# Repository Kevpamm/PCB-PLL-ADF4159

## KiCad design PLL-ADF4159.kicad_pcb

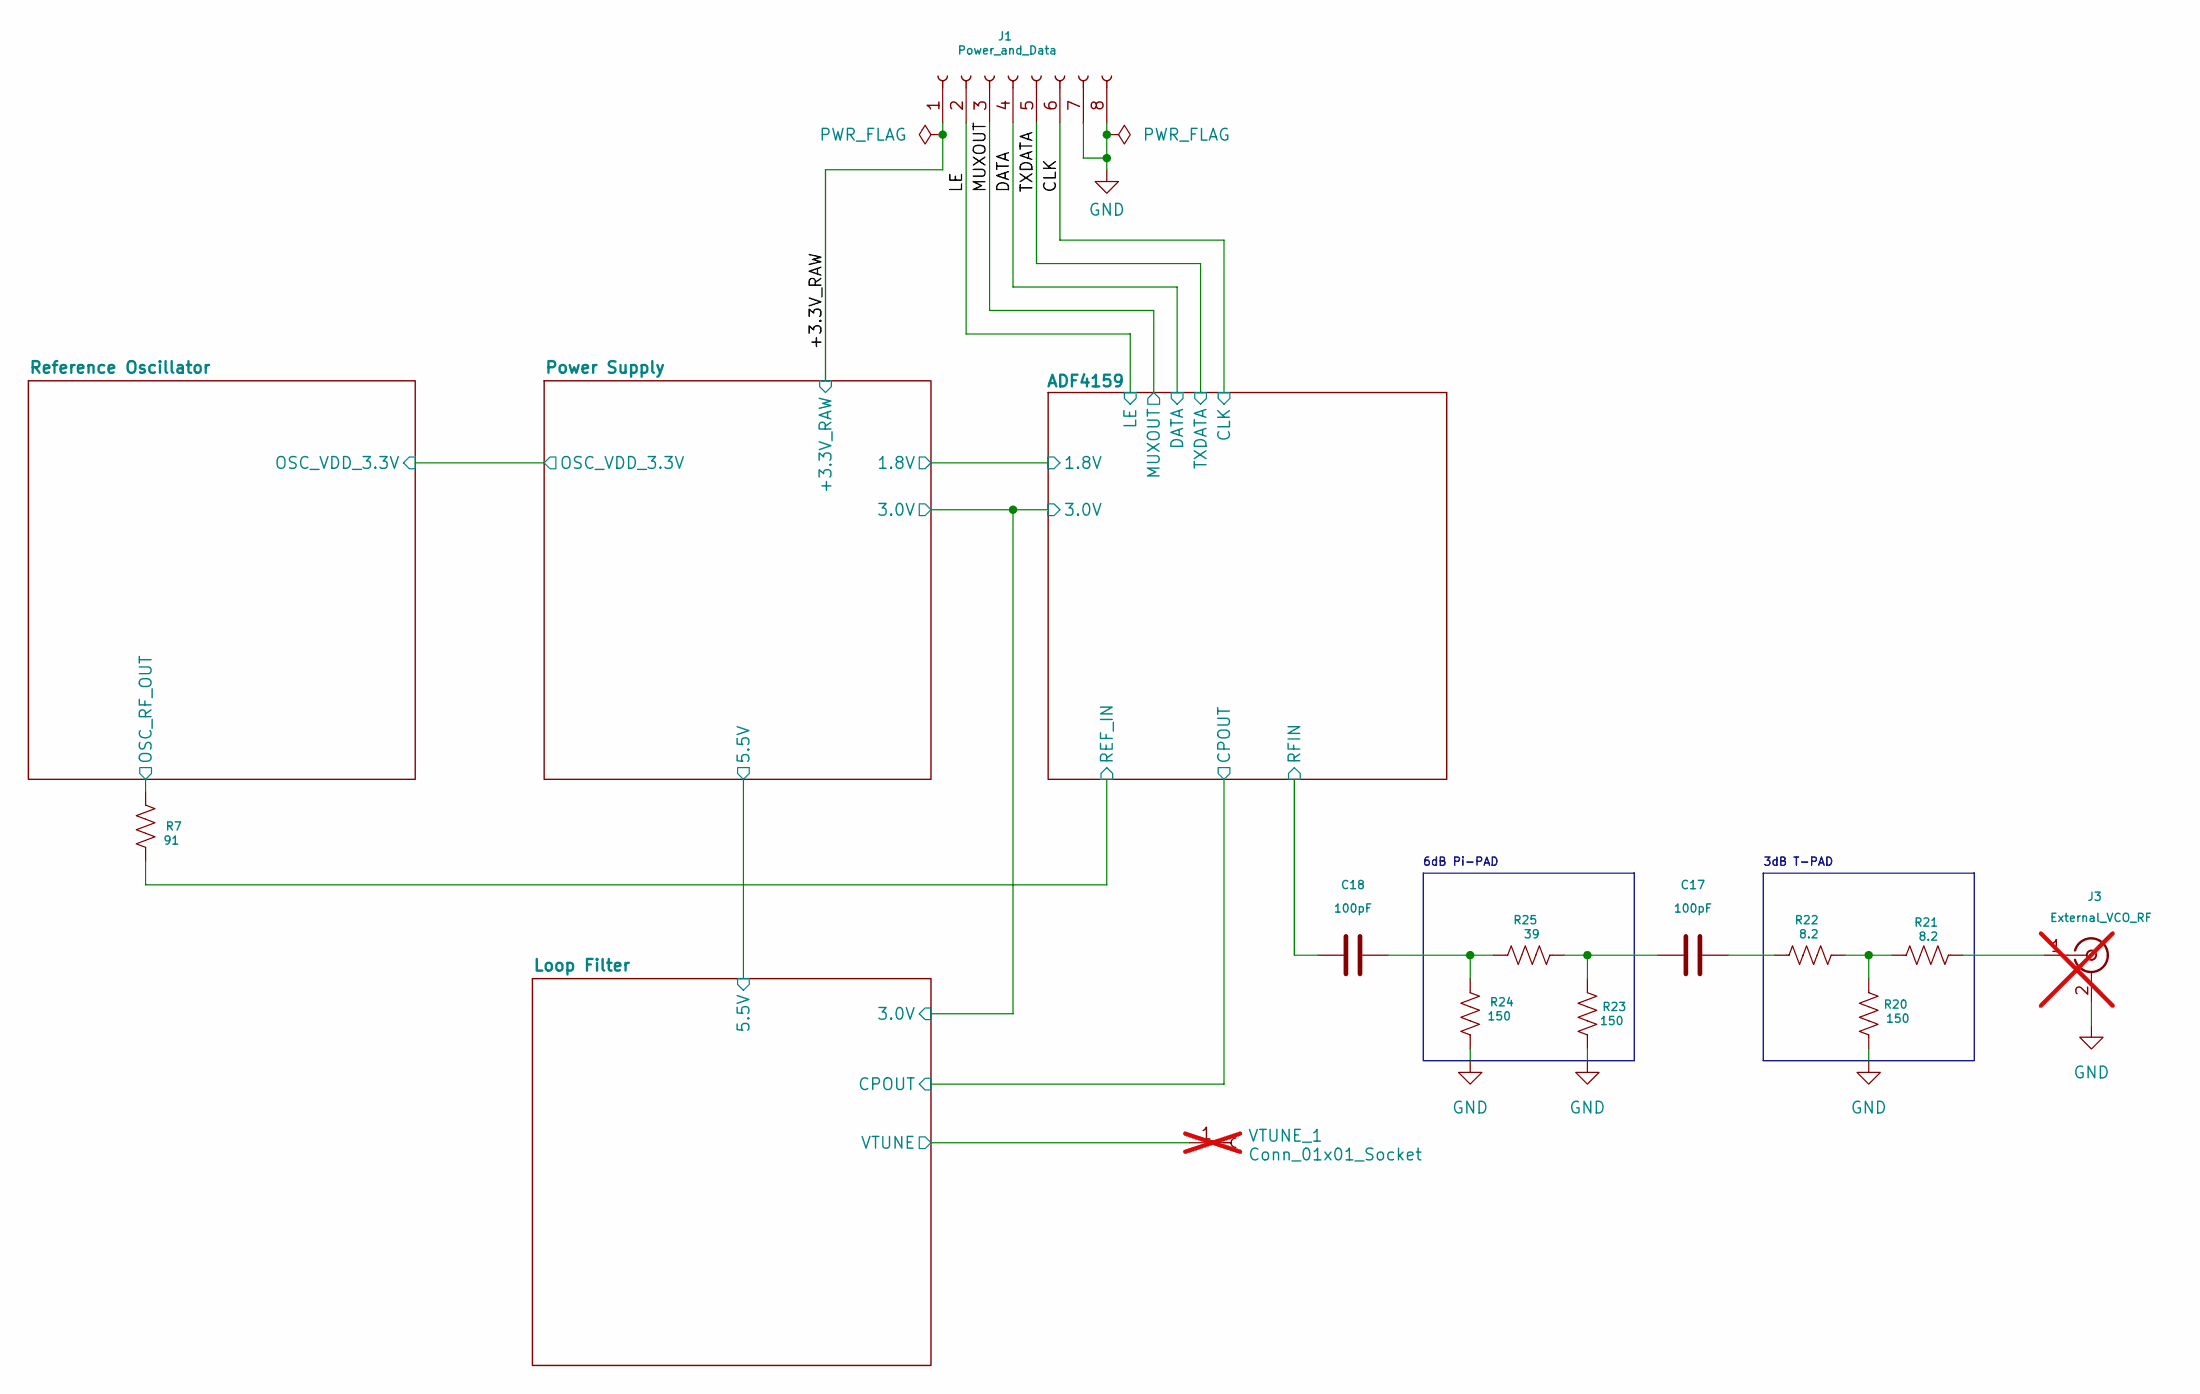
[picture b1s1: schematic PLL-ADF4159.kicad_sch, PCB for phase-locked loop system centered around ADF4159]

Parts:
C17, C18: 100pF; C_0402_1005Metric
J1: Power_and_Data; PinSocket_2x04_P2.54mm_Vertical
J3: External_VCO_RF; SMA_EDGELAUNCH_CUSTOME; not fitted
R7: 91; R_0402_1005Metric
R20: 150; R_0402_1005Metric
R21, R22: 8.2; R_0402_1005Metric; MFR.Part # RTT028R20FTH; JLCPCB Part # C4144
R23, R24: 150; R_0402_1005Metric; MFR.Part # CRCW0402150RFKED; JLCPCB Part # C82683
R25: 39; R_0402_1005Metric; MFR.Part # 0402WGF390JTCE; JLCPCB Part # C25110
VTUNE_1: Conn_01x01_Socket; PinSocket_1x01_P2.54mm_Vertical; not fitted

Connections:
/+3.3V_RAW: J1.1; also elsewhere on the board
/ADF4159/REF_IN: R7.2; also elsewhere on the board
/ADF4159/RFIN: C18.1; also elsewhere on the board
/CLK: J1.6; also elsewhere on the board
/DATA: J1.4; also elsewhere on the board
/LE: J1.2; also elsewhere on the board
/Loop Filter/VTUNE: VTUNE_1.1 (Pin_1_1); also elsewhere on the board
/MUXOUT: J1.3; also elsewhere on the board
/Reference Oscillator/OSC_RF_OUT: R7.1; also elsewhere on the board
/TXDATA: J1.5; also elsewhere on the board
GND: J1.7, J1.8, J3.2 (Ext), R20.2, R23.2, R24.2; also elsewhere on the board
unnamed: C17.1, R23.1, R25.2
unnamed: C17.2, R22.1
unnamed: C18.2, R24.1, R25.1
unnamed: J3.1 (In), R21.2
unnamed: R20.1, R21.1, R22.2

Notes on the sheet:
3dB T-PAD
6dB Pi-PAD

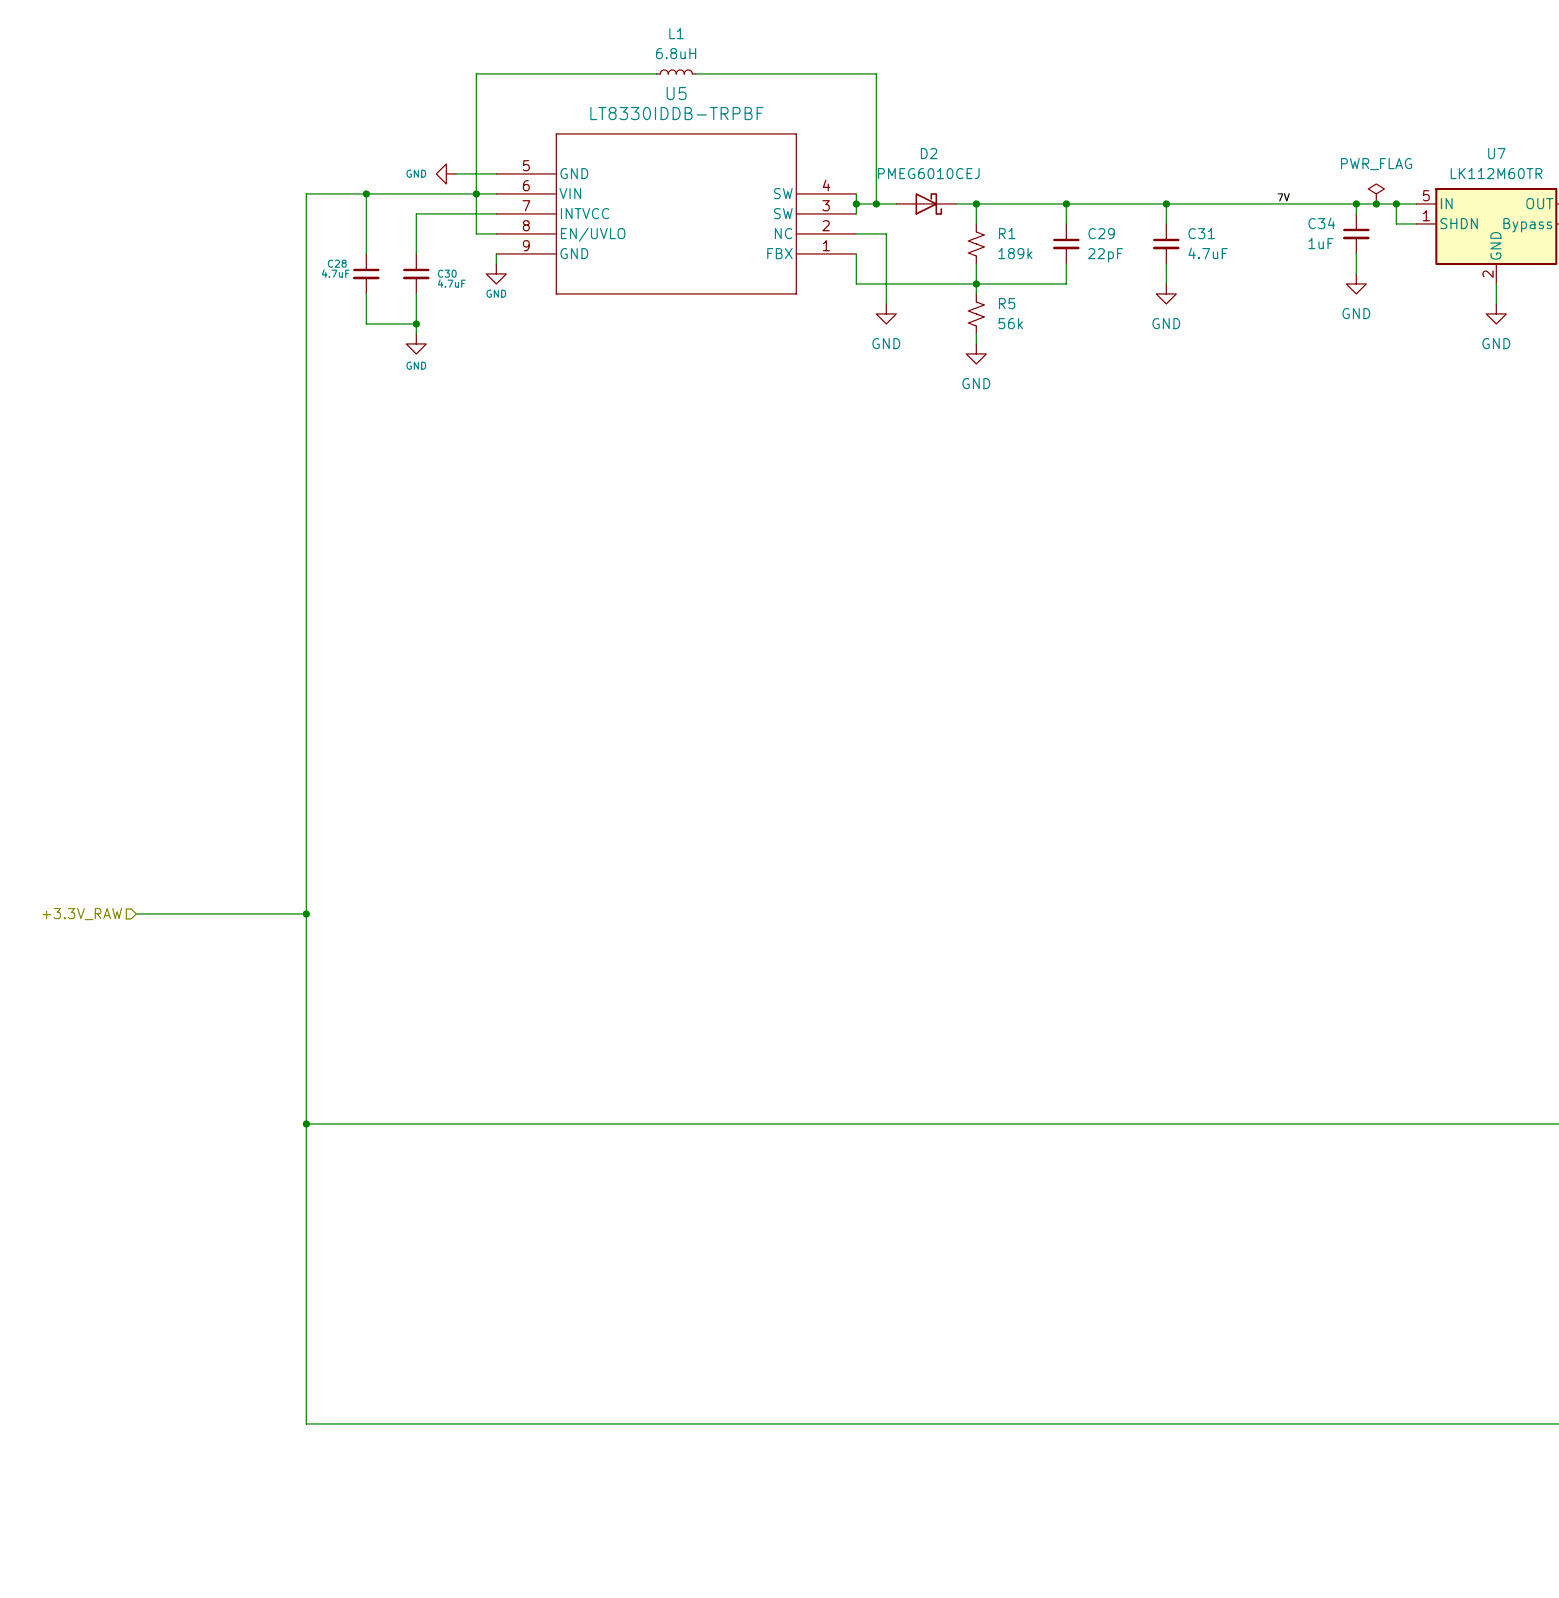
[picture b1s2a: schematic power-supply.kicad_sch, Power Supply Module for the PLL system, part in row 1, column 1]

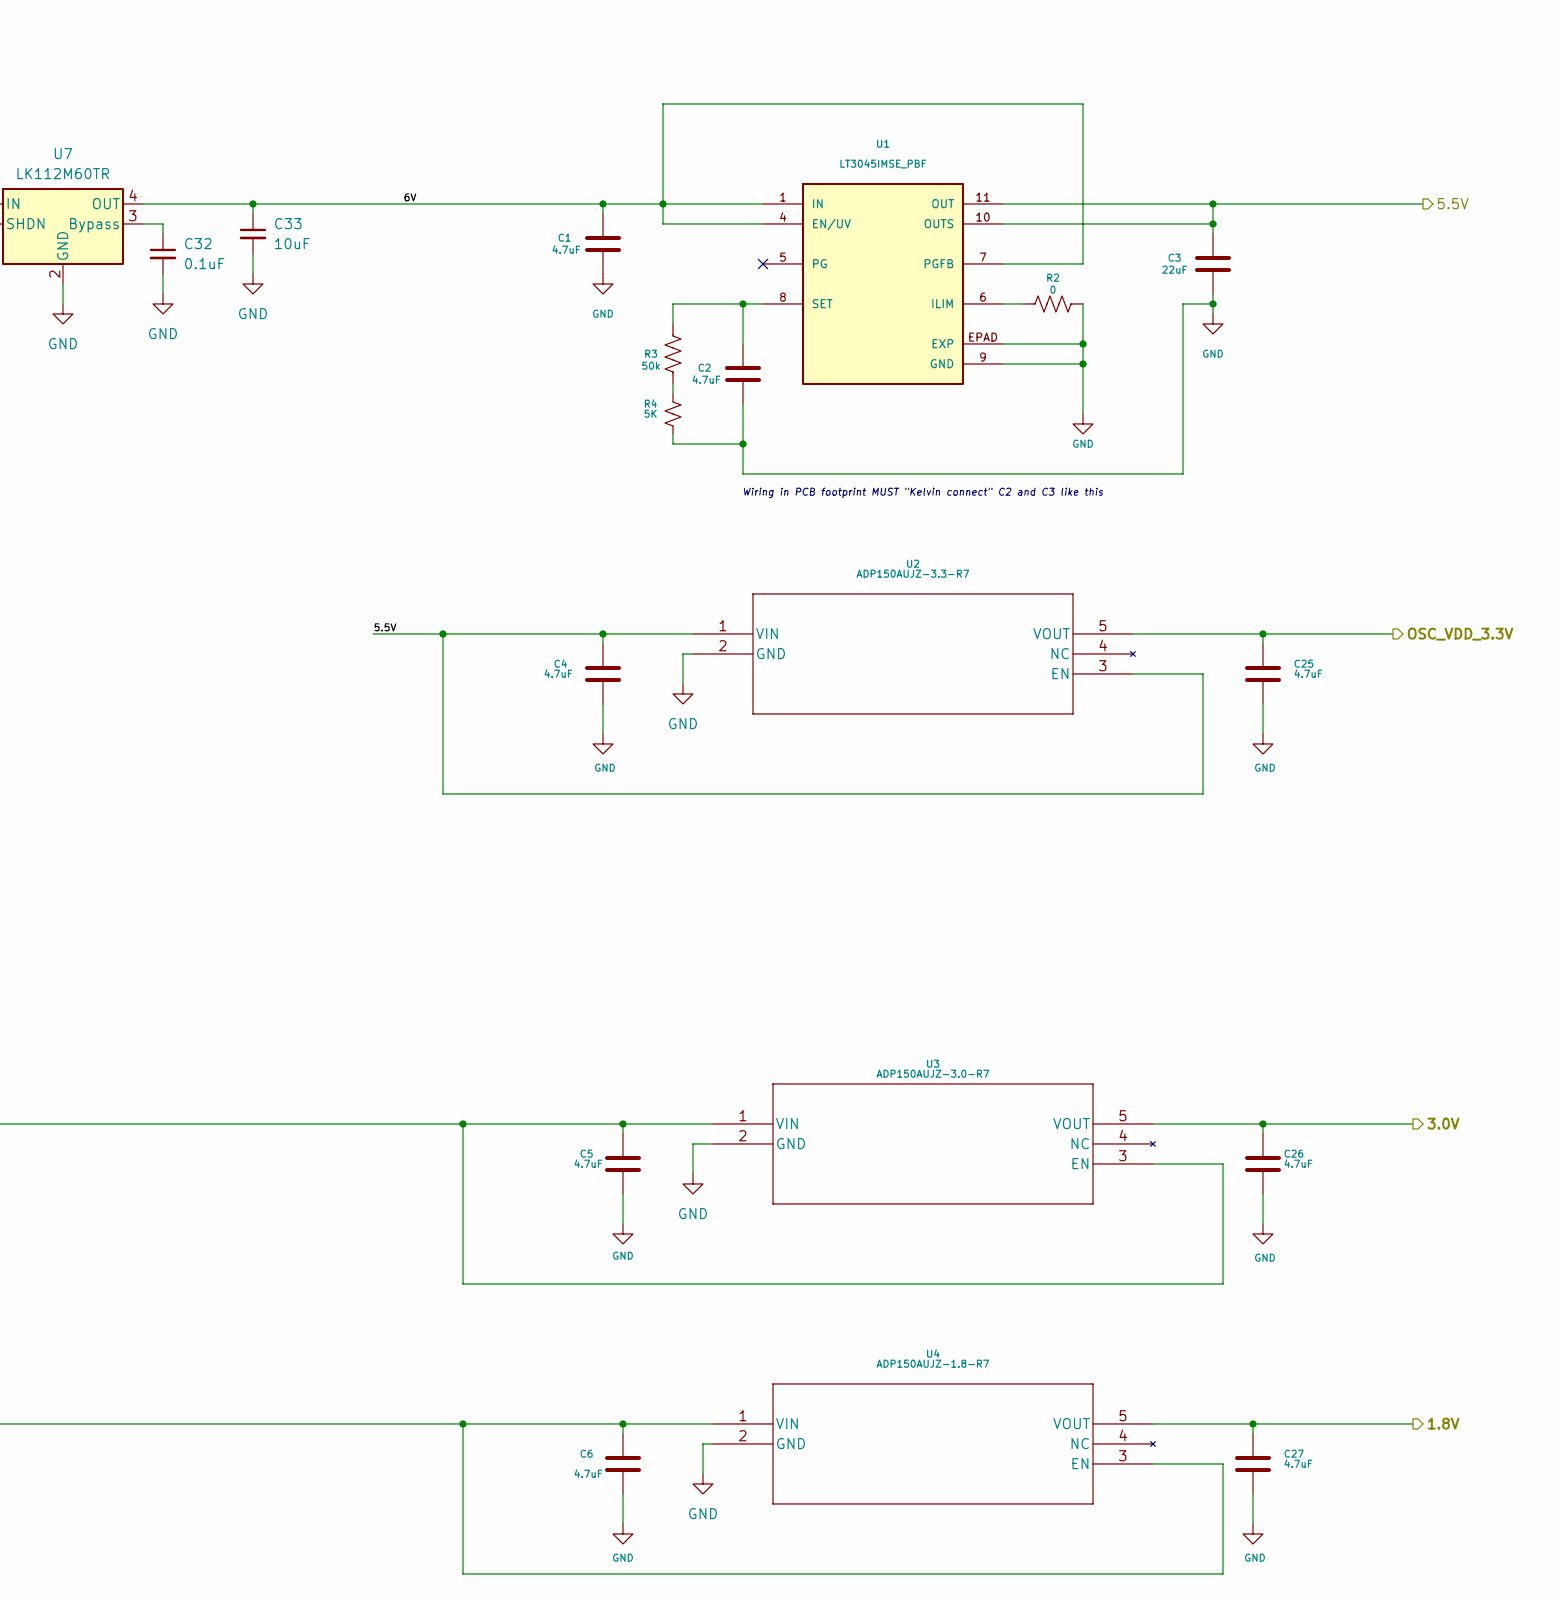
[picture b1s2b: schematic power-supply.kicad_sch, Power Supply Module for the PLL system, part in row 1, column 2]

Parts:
C1, C2, C4, C5, C6, C25, C26, C27, C28, C30, C31: 4.7uF; C_0402_1005Metric
C3: 22uF; C_0603_1608Metric
C29: 22pF; C_0402_1005Metric
C32: 0.1uF; C_0402_1005Metric
C33: 10uF; C_0603_1608Metric
C34: 1uF; C_0402_1005Metric
D2: PMEG6010CEJ; D_SOD-323F
L1: 6.8uH; L_0603_1608Metric
R1: 189k; R_0603_1608Metric
R2: 0; R_0402_1005Metric
R3: 50k; R_0402_1005Metric
R4: 5K; R_0402_1005Metric
R5: 56k; R_0805_2012Metric; MFR.Part # 0603WAF5602T5E; JLCPCB Part # C23206
U1: LT3045IMSE_PBF; MSOP12_MSE_ADI-L; PARTREV D
U2: ADP150AUJZ-3.3-R7; UJ_5_ADI-L
U3: ADP150AUJZ-3.0-R7; UJ_5_ADI-L
U4: ADP150AUJZ-1.8-R7; UJ_5_ADI-L
U5: LT8330IDDB-TRPBF; DDB_05-08-1702_ADI-L
U7: LK112M60TR; SOT-23-5

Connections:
/+3.3V_RAW: C5.1, C6.1, C28.1, L1.1, U3.1 (VIN), U3.3 (EN), U4.1 (VIN), U4.3 (EN), U5.6 (VIN), U5.8 (EN/UVLO); also elsewhere on the board
/ADF4159/1.8V: C27.1, U4.5 (VOUT); also elsewhere on the board
/ADF4159/3.0V: C26.1, U3.5 (VOUT); also elsewhere on the board
/Power Supply/5.5V: C3.1, C4.1, U1.10 (OUTS), U1.11 (OUT), U1.12 (OUT), U2.1 (VIN), U2.3 (EN); also elsewhere on the board
/Power Supply/6V: C1.1, C33.1, U1.1 (IN), U1.2 (IN), U1.3 (IN), U1.4 (EN/UV), U1.7 (PGFB), U7.4 (OUT)
/Power Supply/7V: C29.1, C31.1, C34.1, D2.1 (K), R1.2, U7.1 (SHDN), U7.5 (IN)
/Power Supply/OSC_VDD_3.3V: C25.1, U2.5 (VOUT); also elsewhere on the board
GND: C1.2, C2.2, C3.2, C4.2, C5.2, C6.2, C25.2, C26.2, C27.2, C28.2, C30.2, C31.2, C32.2, C33.2, C34.2, R2.1, R4.2, R5.1, U1.9 (GND), U1.EPAD (EXP), U2.2 (GND), U3.2 (GND), U4.2 (GND), U5.2 (NC), U5.5 (GND), U5.9 (GND), U7.2 (GND); also elsewhere on the board
unnamed: D2.2 (A), L1.2, U5.3 (SW), U5.4 (SW)
unnamed: R3.2, R4.1
unnamed: R2.2, U1.6 (ILIM)
unnamed: C2.1, R3.1, U1.8 (SET)
unnamed: C29.2, R1.1, R5.2, U5.1 (FBX)
unnamed: C30.1, U5.7 (INTVCC)
unnamed: C32.1, U7.3 (Bypass)

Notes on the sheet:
Wiring in PCB footprint MUST "Kelvin connect" C2 and C3 like this

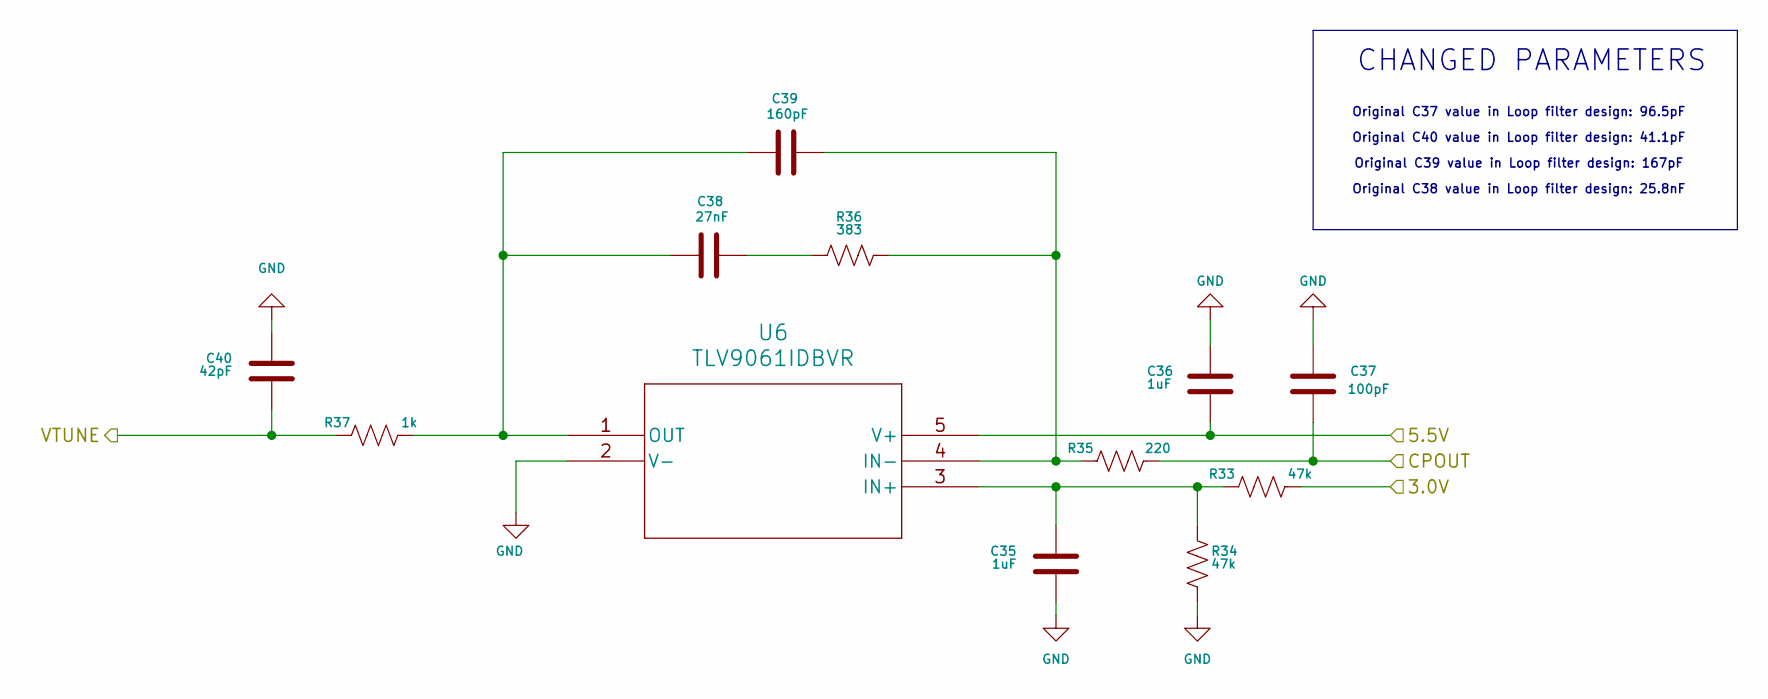
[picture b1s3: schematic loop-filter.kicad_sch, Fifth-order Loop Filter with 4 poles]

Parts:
C35, C36: 1uF; C_0402_1005Metric
C37: 100pF; C_0402_1005Metric
C38: 27nF; C_0402_1005Metric; MFR.Part # C1005X7R273KETS; JLCPCB Part # C147619
C39: 160pF; C_0402_1005Metric
C40: 42pF; C_0603_1608Metric; MFR.Part # 0603CG420J500NT; JLCPCB Part # C3008316
R33, R34: 47k; R_0402_1005Metric
R35: 220; R_0402_1005Metric
R36: 383; R_0402_1005Metric; MFR.Part # 0603WAF3830T5E; JLCPCB Part # C23036
R37: 1k; R_0402_1005Metric
U6: TLV9061IDBVR; DBV5_TEX

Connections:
/ADF4159/3.0V: R33.2; also elsewhere on the board
/ADF4159/CPOUT: C37.2, R35.2; also elsewhere on the board
/Loop Filter/VTUNE: C40.2, R37.2; also elsewhere on the board
/Power Supply/5.5V: C36.1, U6.5 (V+); also elsewhere on the board
GND: C35.2, C36.2, C37.1, C40.1, R34.2, U6.2 (V-); also elsewhere on the board
unnamed: C38.1, R36.1
unnamed: C35.1, R33.1, R34.1, U6.3 (IN+)
unnamed: C39.1, R35.1, R36.2, U6.4 (IN-)
unnamed: C38.2, C39.2, R37.1, U6.1 (OUT)

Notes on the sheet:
Original C40 value in Loop filter design: 41.1pF
Original C39 value in Loop filter design: 167pF
Original C38 value in Loop filter design: 25.8nF
Original C37 value in Loop filter design: 96.5pF
CHANGED PARAMETERS

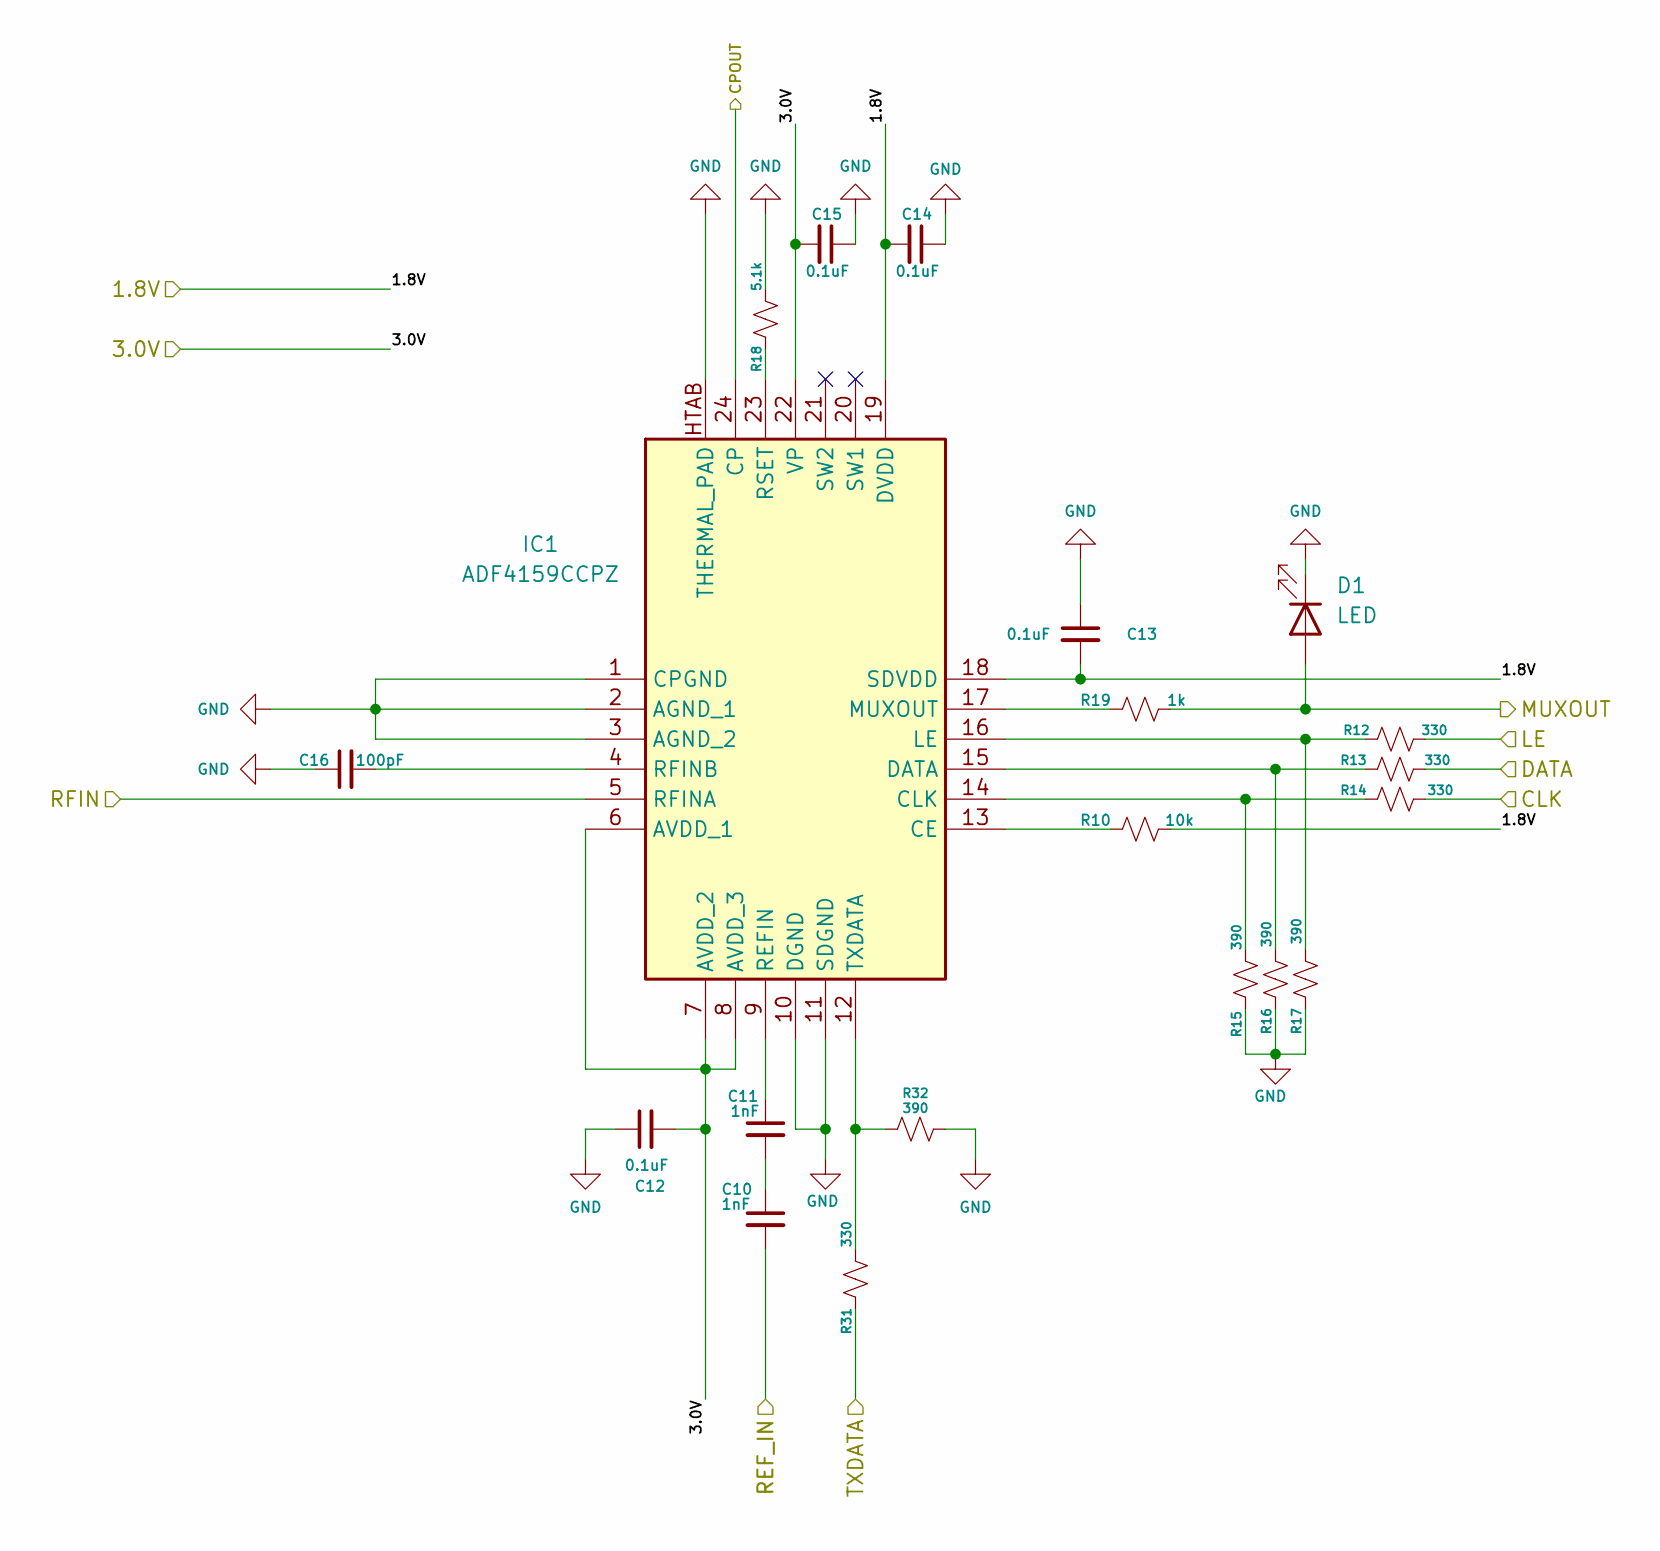
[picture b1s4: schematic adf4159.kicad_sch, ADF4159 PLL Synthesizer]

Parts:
C10, C11: 1nF; C_0402_1005Metric
C12, C13, C14, C15: 0.1uF; C_0402_1005Metric
C16: 100pF; C_0402_1005Metric
D1: LED; LED_0805_2012Metric
IC1: ADF4159CCPZ; CP_24_10_ADI-L; Manufacturer_Part_Number ADF4159CCPZ; Mouser Part Number 584-ADF4159CCPZ
R10: 10k; R_0402_1005Metric
R12, R13, R14, R31: 330; R_0402_1005Metric
R15, R16, R17, R32: 390; R_0402_1005Metric
R18: 5.1k; R_0402_1005Metric
R19: 1k; R_0402_1005Metric

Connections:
/ADF4159/1.8V: C13.2, C14.2, IC1.18 (SDVDD), IC1.19 (DVDD), R10.2; also elsewhere on the board
/ADF4159/3.0V: C12.2, C15.2, IC1.6 (AVDD_1), IC1.7 (AVDD_2), IC1.8 (AVDD_3), IC1.22 (VP); also elsewhere on the board
/ADF4159/CPOUT: IC1.24 (CP); also elsewhere on the board
/ADF4159/REF_IN: C10.2; also elsewhere on the board
/ADF4159/RFIN: IC1.5 (RFINA); also elsewhere on the board
/CLK: R14.2; also elsewhere on the board
/DATA: R13.2; also elsewhere on the board
/LE: R12.2; also elsewhere on the board
/MUXOUT: D1.2 (A), R19.2; also elsewhere on the board
/TXDATA: R31.1; also elsewhere on the board
GND: C12.1, C13.1, C14.1, C15.1, C16.1, D1.1 (K), IC1.1 (CPGND), IC1.2 (AGND_1), IC1.3 (AGND_2), IC1.10 (DGND), IC1.11 (SDGND), IC1.HTAB (THERMAL_PAD), R15.1, R16.1, R17.1, R18.1, R32.2; also elsewhere on the board
unnamed: C10.1, C11.2
unnamed: IC1.13 (CE), R10.1
unnamed: IC1.14 (CLK), R14.1, R15.2
unnamed: IC1.15 (DATA), R13.1, R16.2
unnamed: IC1.16 (LE), R12.1, R17.2
unnamed: IC1.17 (MUXOUT), R19.1
unnamed: C11.1, IC1.9 (REFIN)
unnamed: C16.2, IC1.4 (RFINB)
unnamed: IC1.23 (RSET), R18.2
unnamed: IC1.12 (TXDATA), R31.2, R32.1

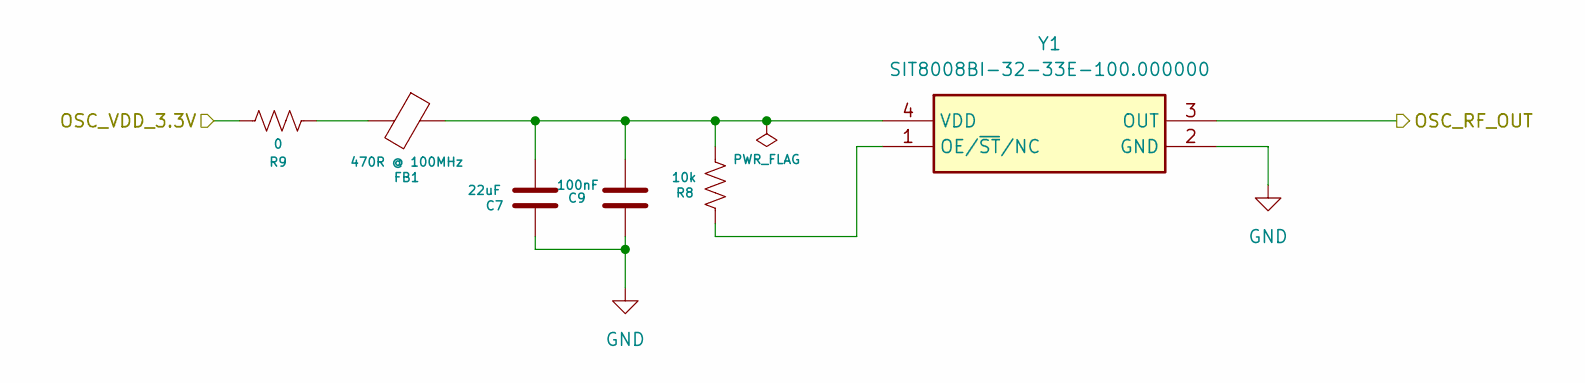
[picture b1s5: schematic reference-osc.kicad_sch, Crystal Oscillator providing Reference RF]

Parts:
C7: 22uF; C_0402_1005Metric
C9: 100nF; C_0402_1005Metric
FB1: 470R @ 100MHz; L_0603_1608Metric; MPN BLM18AG471SZ1D; JLCPCB part: C883591
R8: 10k; R_0402_1005Metric
R9: 0; R_0402_1005Metric
Y1: SIT8008BI-32-33E-100.000000; SiT8921BM3233N127872000; Manufacturer_Part_Number SIT8008BI-32-33E-100.000000

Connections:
/Power Supply/OSC_VDD_3.3V: R9.2; also elsewhere on the board
/Reference Oscillator/OSC_RF_OUT: Y1.3 (OUT); also elsewhere on the board
GND: C7.1, C9.1, Y1.2 (GND); also elsewhere on the board
unnamed: FB1.2, R9.1
unnamed: R8.1, Y1.1 (OE/~ST/NC)
unnamed: C7.2, C9.2, FB1.1, R8.2, Y1.4 (VDD)

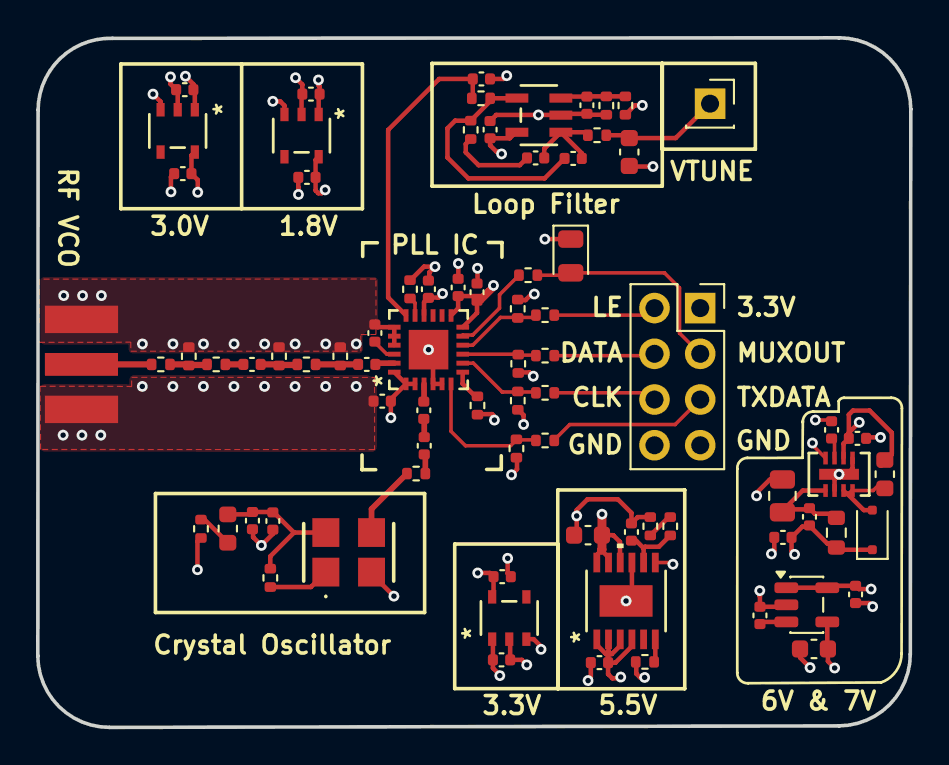
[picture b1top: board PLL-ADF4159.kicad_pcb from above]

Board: 4 copper layers, 48.5 x 38.3 mm, 79 parts (0 on the bottom side), 47 nets.
